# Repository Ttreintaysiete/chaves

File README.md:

# chaves
Cheap Hacky Audio/Video - Glitch VGA synth based on jonasbers.com/chav/

This is a WIP, and PCBs have not fully tested, if you want to contribute send a build to your favorite pcb provider and give us any feedback.

Pending...

* will generate a bom
* building guide

## Chaves

Its a glitch video synth bassed on CHA/V as stated, but with lots of controls and patcheable pins with the intentions of doing a mini-modular video glitch synth.

Like in the original CHA/V it has 6 VCOs, with selectables ranges, sync sources, frequency and effects outputs (thanks to the coupling caps). Here is a schematic of a single voice

* The __syncbus__ can be either connected to the vsyn or hsync of the VGA tester. This will send the selected sync to the jumperpins near the beggining of the Oscillator so you can either select each oscillator to be connected to this sync bus or not to be free running.
* Since we are using pinheaders you can use patcables from any point of the pcb so anthoer oscillator can __modulate__ the sync of a specific oscillator...
* Every voice output can be connected to any of the RGA VGA inputs with patchables, or can be patched somewhere else, to create complex patterns

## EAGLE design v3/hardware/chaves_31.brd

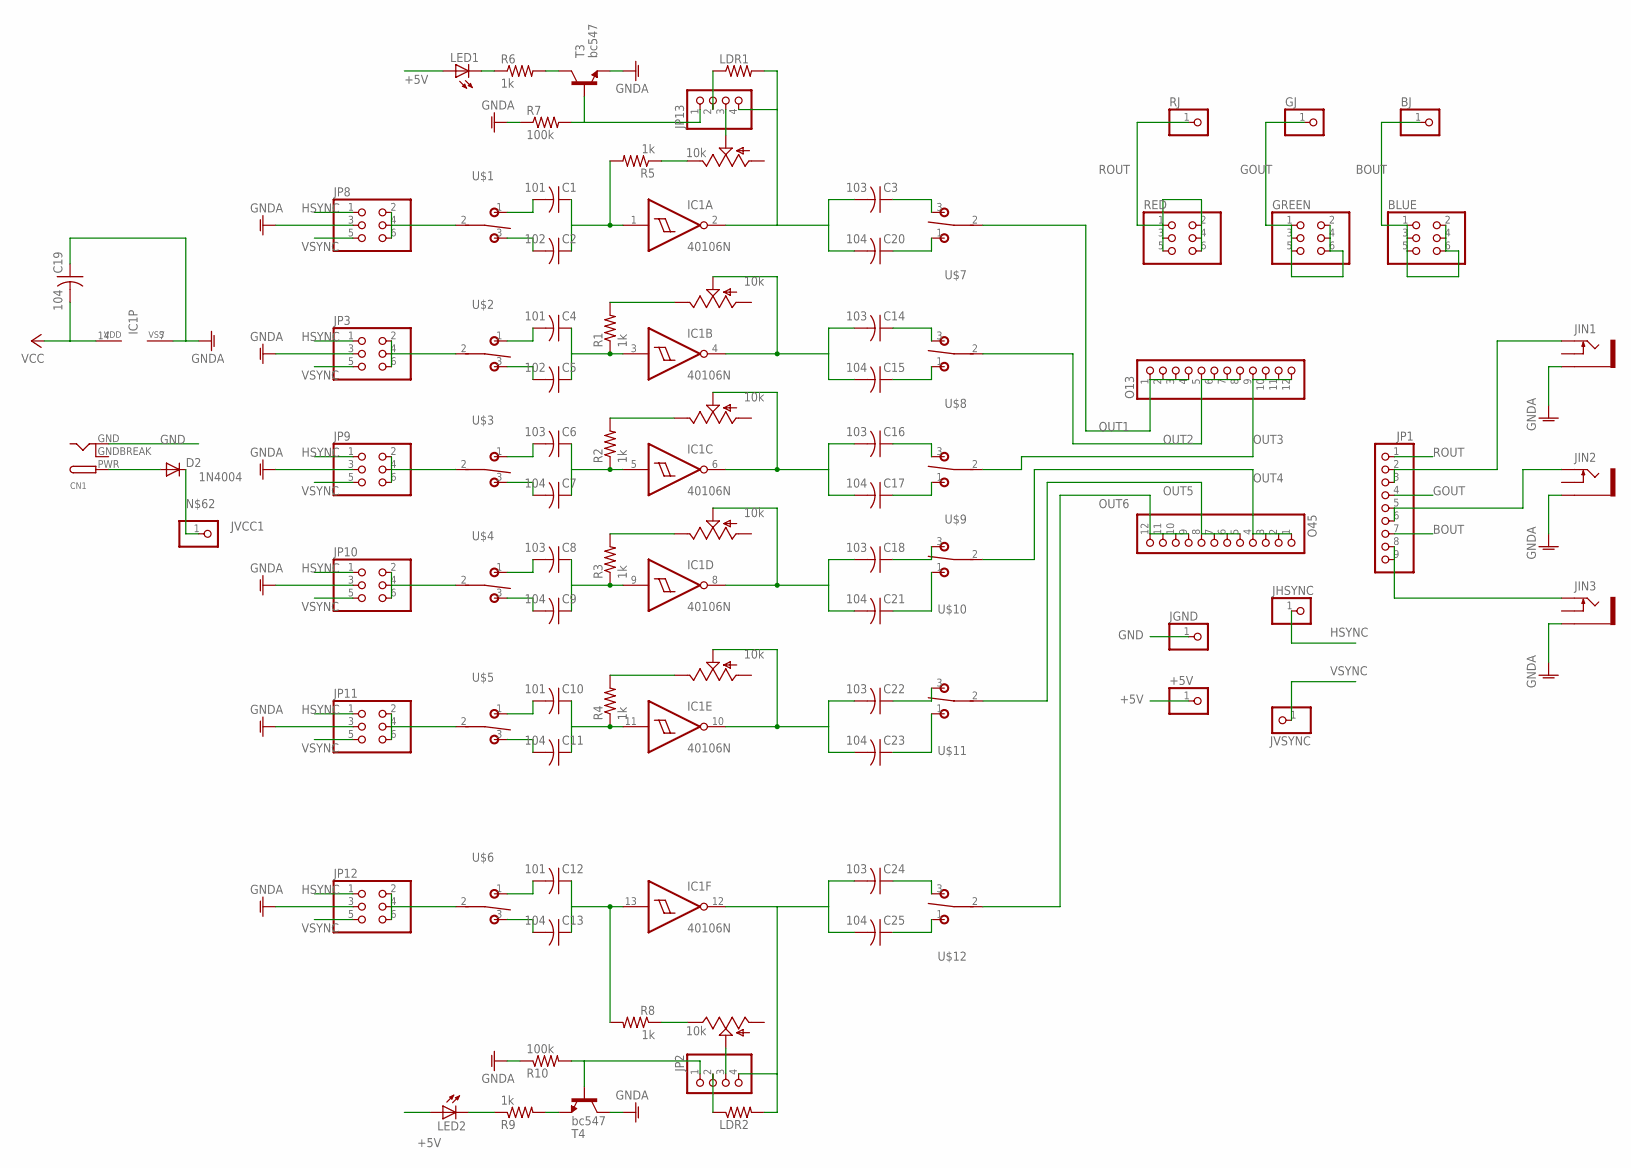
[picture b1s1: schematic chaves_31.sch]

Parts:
+5V: PINHD-1X1; 1X01
BJ: PINHD-1X1; 1X01
BLUE: PINHD-2X3; 2X03
C1, C4, C10, C12: 101; C050-025X075
C2, C5: 102; C050-025X075
C3, C6, C8, C14, C16, C18, C22, C24: 103; C050-025X075
C7, C9, C11, C13, C15, C17, C19, C20, C21, C23, C25: 104; C050-025X075
CN1: DCBARRELPTH; DCJACK_2MM_PTH
D2: 1N4004; DO41-10
GJ: PINHD-1X1; 1X01
GREEN: PINHD-2X3; 2X03
IC1: 40106N; DIL14
JGND: PINHD-1X1; 1X01
JHSYNC: PINHD-1X1; 1X01
JIN1, JIN2, JIN3: PJ302M
JP1: PINHD-1X9; 1X09-BIG
JP2, JP13: PINHD-1X4; 1X04
JP3, JP8, JP9, JP10, JP11, JP12: PINHD-2X3; 2X03
JVCC1: PINHD-1X1; 1X01
JVSYNC: PINHD-1X1; 1X01
LDR1, LDR2: R-US_0204/2V; 0204V
LED1, LED2: LED5MM
O13, O45: PINHD-1X12-CB; 1X12-CB
POT1, POT2, POT3, POT4, POT5, POT6: 10k; ALPS_POT_VERTICAL
R1, R2, R3, R4, R5, R6, R8, R9: 1k; 0204V
R7, R10: 100k; 0204V
RED: PINHD-2X3; 2X03
RJ: PINHD-1X1; 1X01
T3, T4: bc547; TO92-CBE
U$1, U$2, U$3, U$4, U$5, U$6, U$7, U$8, U$9, U$10, U$11, U$12: T-80-T-SPDT-ON-OFF-ON; M9040P

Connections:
+5V: +5V.1, C19.2, IC1.14 (VDD), LED1.A, LED2.A
BOUT: BJ.1, BLUE.1, BLUE.2, BLUE.3, BLUE.4, BLUE.5, BLUE.6, JP1.7
GND: C19.1, CN1.GND, IC1.7 (VSS), JGND.1, JIN1.GND (SLEEVE), JIN2.GND (SLEEVE), JIN3.GND (SLEEVE), JP3.3, JP8.3, JP9.3, JP10.3, JP11.3, JP12.3, R7.1, R10.1, T3.E, T4.C
GNDBREAK: CN1.GNDBREAK
GOUT: GJ.1, GREEN.1, GREEN.2, GREEN.3, GREEN.4, GREEN.5, GREEN.6, JP1.4
HSYNC: JHSYNC.1, JP3.1, JP8.1, JP9.1, JP10.1, JP11.1, JP12.1
unnamed: C1.2, U$1.1 (O)
unnamed: C2.2, U$1.3 (S)
unnamed: JP13.2, LDR1.1
unnamed: C5.2, U$2.3 (S)
unnamed: C4.2, U$2.1 (O)
unnamed: JP13.3, POT1.P$2 (S)
unnamed: C8.2, U$4.1 (O)
unnamed: C9.2, U$4.3 (S)
unnamed: JIN1.TIP, JP1.2, JP1.3
unnamed: C6.2, U$3.1 (O)
unnamed: C7.2, U$3.3 (S)
unnamed: JIN2.TIP, JP1.5, JP1.6
unnamed: JIN3.TIP, JP1.8, JP1.9
unnamed: JP3.2, JP3.4, JP3.6, U$2.2
unnamed: R6.2, T3.C
unnamed: C20.1, U$7.1 (O)
unnamed: C3.1, U$7.3 (S)
unnamed: LED1.K (C), R6.1
unnamed: POT1.P$1 (E), R5.1
unnamed: JP8.2, JP8.4, JP8.6, U$1.2
unnamed: LED2.K (C), R9.1
unnamed: POT2.P$1 (E), R1.2
unnamed: JP9.2, JP9.4, JP9.6, U$3.2
unnamed: C15.1, U$8.1 (O)
unnamed: R9.2, T4.E
unnamed: C14.1, U$8.3 (S)
unnamed: C17.1, U$9.1 (O)
unnamed: C16.1, U$9.3 (S)
unnamed: JP10.2, JP10.4, JP10.6, U$4.2
unnamed: JP13.1, R7.2, T3.B
unnamed: POT3.P$1 (E), R2.2
unnamed: JP11.2, JP11.4, JP11.6, U$5.2
unnamed: JP12.2, JP12.4, JP12.6, U$6.2
unnamed: C21.1, U$10.1 (O)
unnamed: C18.1, U$10.3 (S)
unnamed: C23.1, U$11.1 (O)
unnamed: C22.1, U$11.3 (S)
unnamed: C25.1, U$12.1 (O)
unnamed: C24.1, U$12.3 (S)
unnamed: C10.2, U$5.1 (O)
unnamed: POT4.P$1 (E), R3.2
unnamed: C11.2, U$5.3 (S)
unnamed: C13.2, U$6.3 (S)
unnamed: C12.2, U$6.1 (O)
unnamed: POT5.P$1 (E), R4.2
unnamed: C24.2, C25.2, IC1.12 (O), JP2.4, LDR2.2
unnamed: JP2.2, LDR2.1
unnamed: JP2.3, POT6.P$2 (S)
unnamed: POT6.P$1 (E), R8.1
unnamed: JP2.1, R10.2, T4.B
unnamed: D2.C, JVCC1.1
unnamed: C3.2, C20.2, IC1.2 (O), JP13.4, LDR1.2
unnamed: C14.2, C15.2, IC1.4 (O), POT2.P$2 (S)
unnamed: C16.2, C17.2, IC1.6 (O), POT3.P$2 (S)
unnamed: C18.2, C21.2, IC1.8 (O), POT4.P$2 (S)
unnamed: C22.2, C23.2, IC1.10 (O), POT5.P$2 (S)
OUT1: O13.1, O13.2, O13.3, O13.4, U$7.2
OUT2: O13.5, O13.6, O13.7, O13.8, U$8.2
OUT3: O13.9, O13.10, O13.11, O13.12, U$9.2
OUT4: O45.1, O45.2, O45.3, O45.4, U$10.2
OUT5: O45.5, O45.6, O45.7, O45.8, U$11.2
OUT6: O45.9, O45.10, O45.11, O45.12, U$12.2
ROUT: JP1.1, RED.1, RED.2, RED.3, RED.4, RED.5, RED.6, RJ.1
SS1: C1.1, C2.1, IC1.1 (I), R5.2
SS2: C4.1, C5.1, IC1.3 (I), R1.1
SS3: C6.1, C7.1, IC1.5 (I), R2.1
SS4: C8.1, C9.1, IC1.9 (I), R3.1
SS5: C10.1, C11.1, IC1.11 (I), R4.1
SS6: C12.1, C13.1, IC1.13 (I), R8.2
VIN: CN1.PWR, D2.A
VSYNC: JP3.5, JP8.5, JP9.5, JP10.5, JP11.5, JP12.5, JVSYNC.1

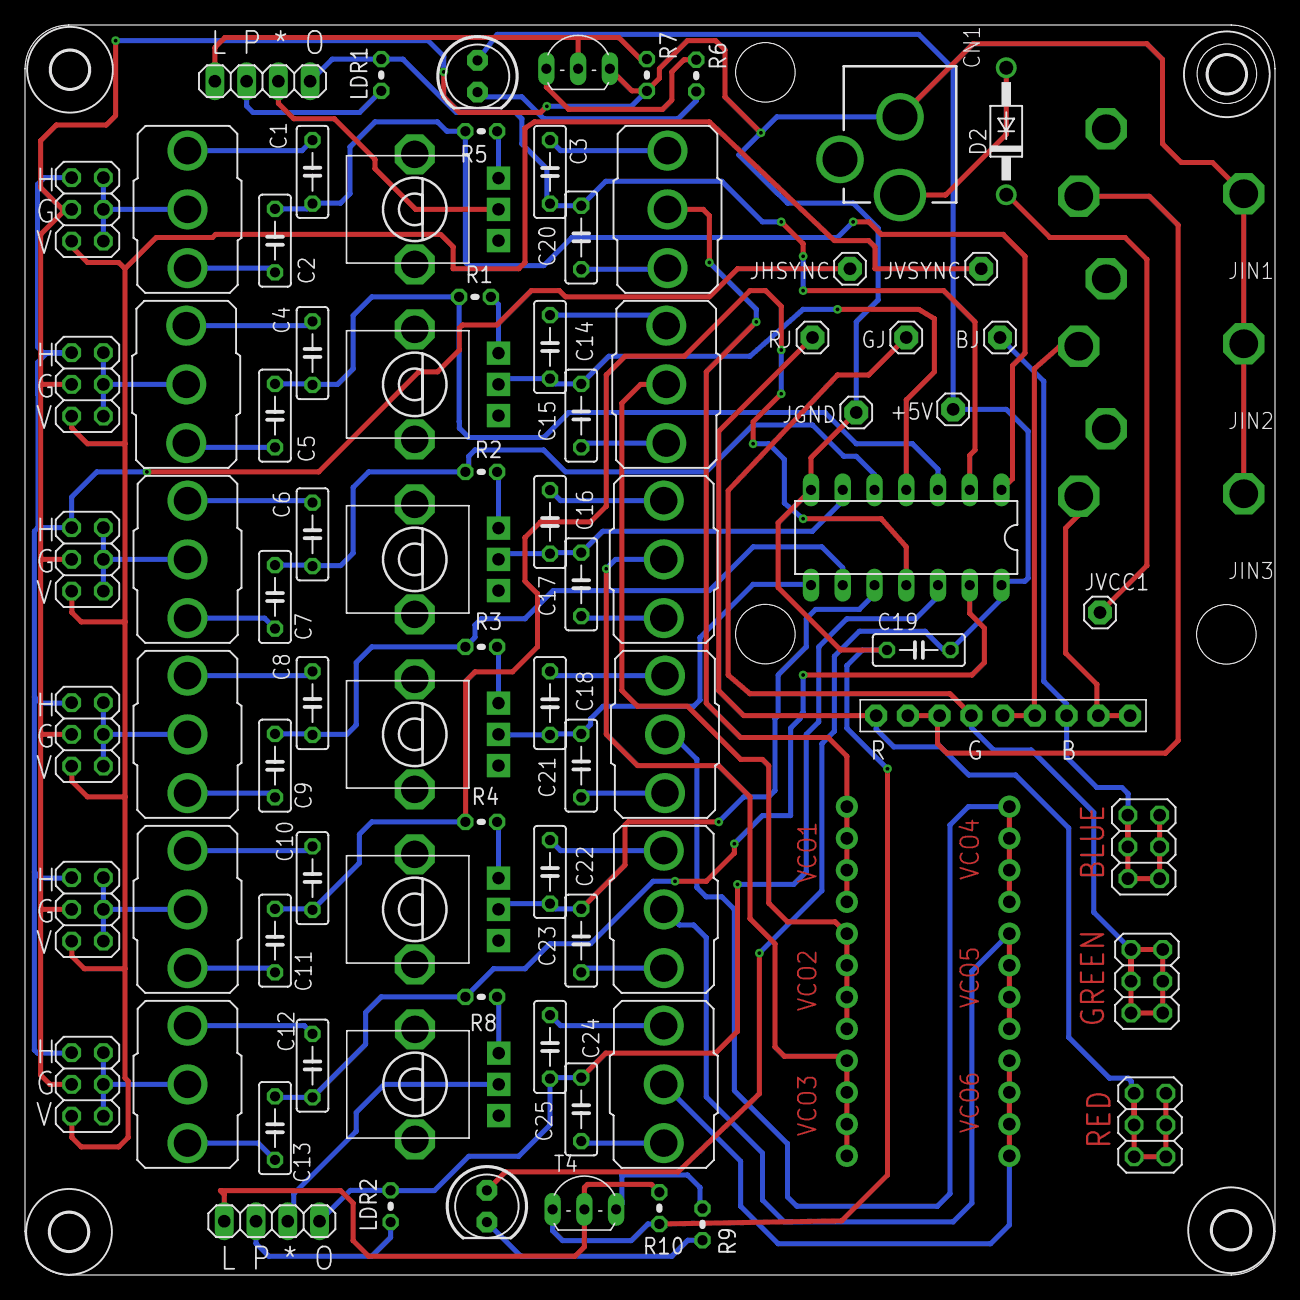
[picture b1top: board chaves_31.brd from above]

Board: 2 copper layers, 100.0 x 100.0 mm, 95 parts (0 on the bottom side), 76 nets.

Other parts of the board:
E$1, E$2, E$3, E$4: DRILL_0.1875
E$5, E$6, E$7, E$8: 3,0

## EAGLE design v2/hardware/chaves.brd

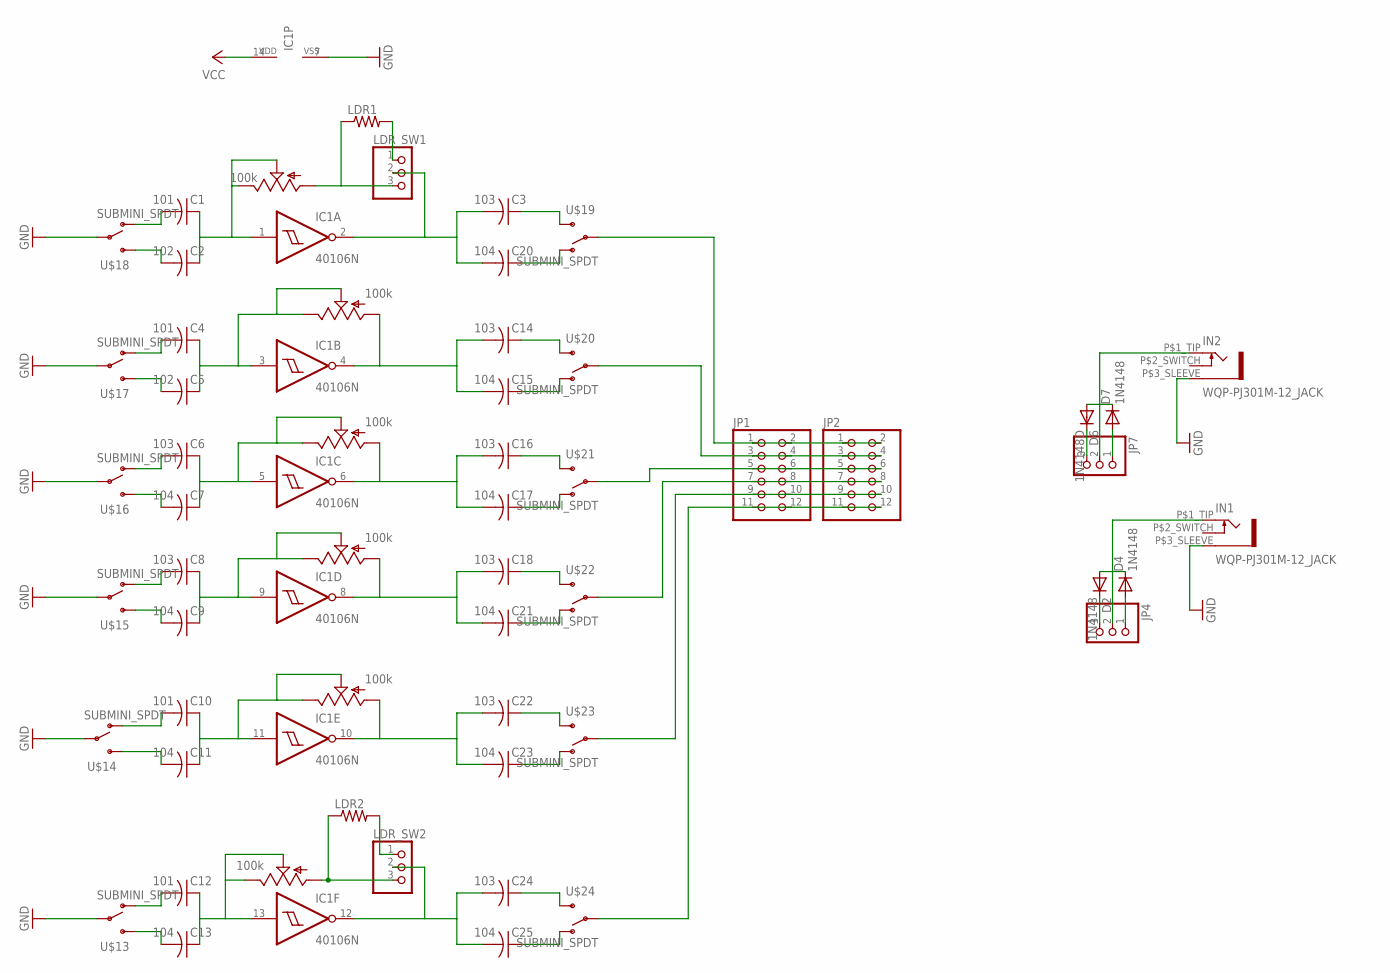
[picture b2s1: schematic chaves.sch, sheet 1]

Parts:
C1, C4, C10, C12: 101; C050-025X075
C2, C5: 102; C050-025X075
C3, C6, C8, C14, C16, C18, C22, C24: 103; C050-025X075
C7, C9, C11, C13, C15, C17, C20, C21, C23, C25: 104; C050-025X075
D2, D4, D7: 1N4148; DO35-7
D6: 1N4148D; DO35-7
IC1: 40106N; DIL14
IN1, IN2: WQP-PJ301M-12_JACK
JP1, JP2: PINHD-2X6; 2X06
JP4, JP7: PINHD-1X3CB; 1X03-CLEANBIG
LDR1, LDR2: R-US_0204/7; 0204/7
LDR_SW1, LDR_SW2: PINHD-1X3; 1X03
POT1, POT2, POT3, POT4, POT5, POT6: 100k; ALPS_POT_VERTICAL
U$13, U$14, U$15, U$16, U$17, U$18, U$19, U$20, U$21, U$22, U$23, U$24: SUBMINI_SPDT; SUBMINI_TOGGLE

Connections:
GND: IC1.7 (VSS), IN1.P$3_SLEEVE (1), IN2.P$3_SLEEVE (1), U$13.COM (COMMON), U$14.COM (COMMON), U$15.COM (COMMON), U$16.COM (COMMON), U$17.COM (COMMON), U$18.COM (COMMON); also elsewhere on the board
GND1: C3.2, C20.2, IC1.2 (O), LDR_SW1.2
GND2: C14.2, C15.2, IC1.4 (O), POT2.P$3 (A)
GND3: C16.2, C17.2, IC1.6 (O), POT3.P$3 (A)
GND4: C18.2, C21.2, IC1.8 (O), POT4.P$3 (A)
GND5: C22.2, C23.2, IC1.10 (O), POT5.P$3 (A)
GND6: C24.2, C25.2, IC1.12 (O), LDR_SW2.2
unnamed: C1.2, U$18.1 (O)
unnamed: C2.2, U$18.3 (S)
unnamed: LDR2.2, LDR_SW2.1
unnamed: C5.2, U$17.3 (S)
unnamed: C4.2, U$17.1 (O)
unnamed: LDR1.2, LDR_SW1.1
unnamed: C8.2, U$15.1 (O)
unnamed: C9.2, U$15.3 (S)
unnamed: D6.A, D7.C, IN2.P$1_TIP (2), JP7.2
unnamed: C6.2, U$16.1 (O)
unnamed: C7.2, U$16.3 (S)
unnamed: C20.1, U$19.1 (O)
unnamed: C3.1, U$19.3 (S)
unnamed: JP1.1, JP1.2, JP2.1, JP2.2, U$19.COM (COMMON)
unnamed: LDR1.1, LDR_SW1.3, POT1.P$3 (A)
unnamed: LDR2.1, LDR_SW2.3, POT6.P$3 (A)
unnamed: D2.A, D4.C, IN1.P$1_TIP (2), JP4.2
unnamed: C15.1, U$20.1 (O)
unnamed: C14.1, U$20.3 (S)
unnamed: JP1.3, JP1.4, JP2.3, JP2.4, U$20.COM (COMMON)
unnamed: C17.1, U$21.1 (O)
unnamed: C16.1, U$21.3 (S)
unnamed: JP1.5, JP1.6, JP2.5, JP2.6, U$21.COM (COMMON)
unnamed: C1.1, C2.1, IC1.1 (I), POT1.P$1 (E), POT1.P$2 (S)
unnamed: C4.1, C5.1, IC1.3 (I), POT2.P$1 (E), POT2.P$2 (S)
unnamed: C6.1, C7.1, IC1.5 (I), POT3.P$1 (E), POT3.P$2 (S)
unnamed: C8.1, C9.1, IC1.9 (I), POT4.P$1 (E), POT4.P$2 (S)
unnamed: C21.1, U$22.1 (O)
unnamed: C18.1, U$22.3 (S)
unnamed: JP1.7, JP1.8, JP2.7, JP2.8, U$22.COM (COMMON)
unnamed: C23.1, U$23.1 (O)
unnamed: C22.1, U$23.3 (S)
unnamed: JP1.9, JP1.10, JP2.9, JP2.10, U$23.COM (COMMON)
unnamed: C25.1, U$24.1 (O)
unnamed: C24.1, U$24.3 (S)
unnamed: JP1.11, JP1.12, JP2.11, JP2.12, U$24.COM (COMMON)
unnamed: C10.2, U$14.1 (O)
unnamed: C10.1, C11.1, IC1.11 (I), POT5.P$1 (E), POT5.P$2 (S)
unnamed: C11.2, U$14.3 (S)
unnamed: C13.2, U$13.3 (S)
unnamed: C12.2, U$13.1 (O)
unnamed: C12.1, C13.1, IC1.13 (I), POT6.P$1 (E), POT6.P$2 (S)
unnamed: D2.C, JP4.3
unnamed: D4.A, JP4.1
unnamed: D6.C, JP7.3
unnamed: D7.A, JP7.1
VCC: IC1.14 (VDD); also elsewhere on the board

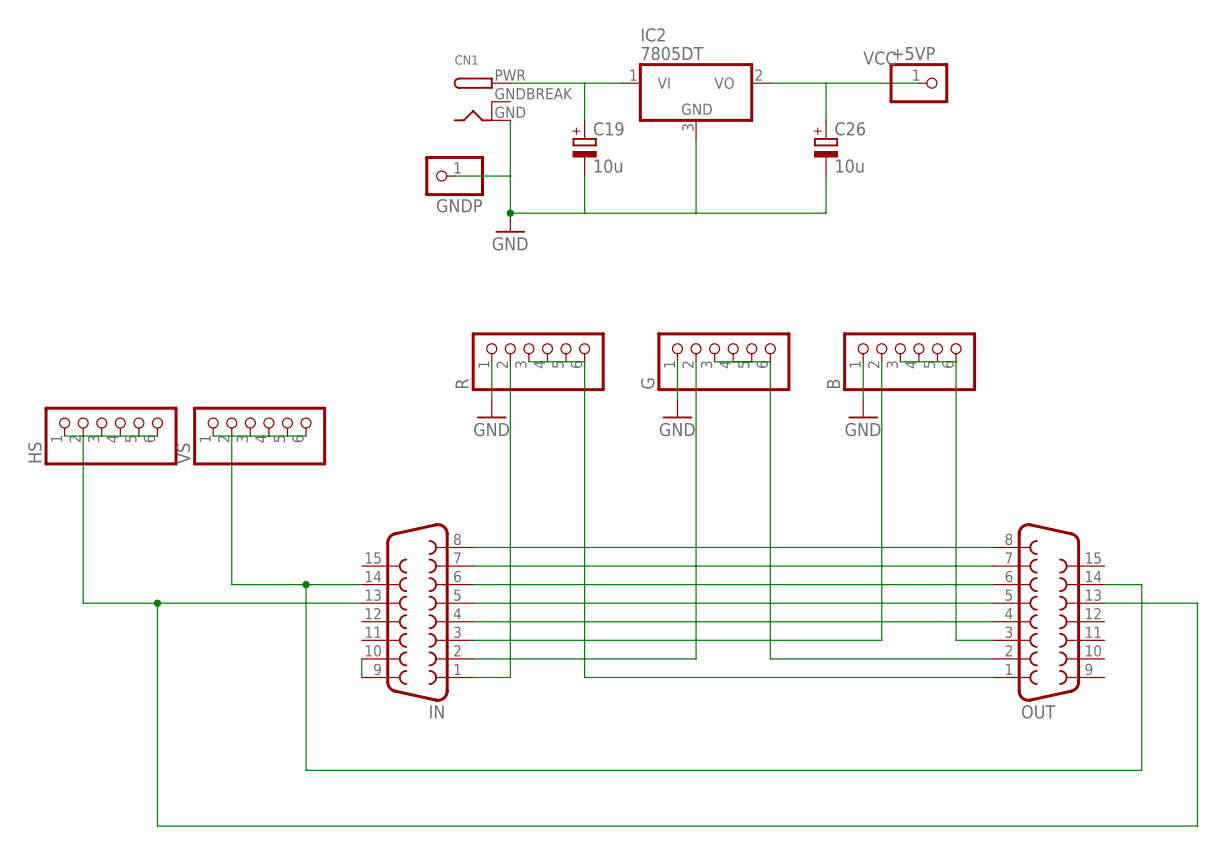
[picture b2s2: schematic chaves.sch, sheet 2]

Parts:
+5VP: PINHD-1X1CB; 1X01-CLEANBIG
B: PINHD-1X6CLEAN; 1X06-CLEAN
C19, C26: 10u; E2,5-5
CN1: DCBARRELPTH; DCJACK_2MM_PTH
G: PINHD-1X6CLEAN; 1X06-CLEAN
GNDP: PINHD-1X1CB; 1X01-CLEANBIG
HS: PINHD-1X6CLEAN; 1X06-CLEAN
IC2: 7805DT; TO252
IN: F15HDH; HDF15H
OUT: F15HDH; HDF15H
R: PINHD-1X6CLEAN; 1X06-CLEAN
VS: PINHD-1X6CLEAN; 1X06-CLEAN

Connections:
GND: B.1, C19.-, C26.-, CN1.GND, G.1, GNDP.1, IC2.3 (GND), IN.4, IN.5, IN.6, IN.7, IN.8, IN.9, IN.10, OUT.4, OUT.5, OUT.6, OUT.7, OUT.8, R.1; also elsewhere on the board
GNDBREAK: CN1.GNDBREAK
unnamed: IN.1, R.2
unnamed: OUT.1, R.3, R.4, R.5, R.6
unnamed: G.2, IN.2
unnamed: G.3, G.4, G.5, G.6, OUT.2
unnamed: B.2, IN.3
unnamed: B.3, B.4, B.5, B.6, OUT.3
unnamed: IN.14, OUT.14, VS.1, VS.2, VS.3, VS.4, VS.5, VS.6
unnamed: HS.1, HS.2, HS.3, HS.4, HS.5, HS.6, IN.13, OUT.13
unnamed: C19.+, CN1.PWR, IC2.1 (VI)
VCC: +5VP.1, C26.+, IC2.2 (VO); also elsewhere on the board

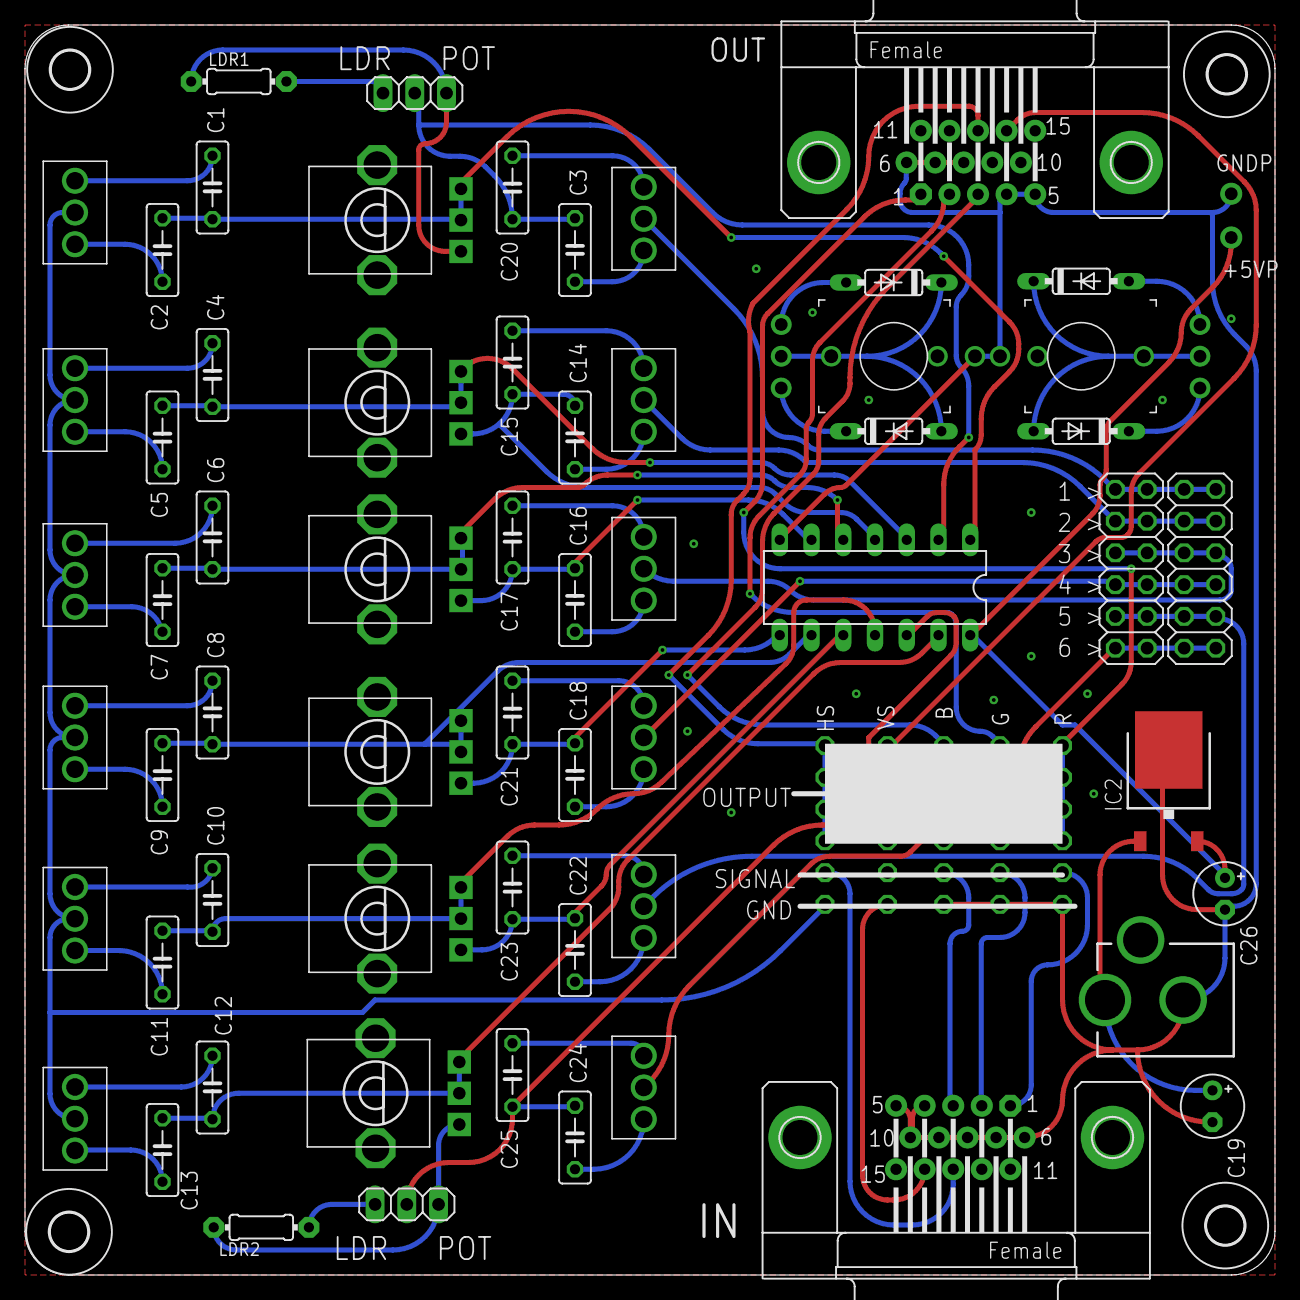
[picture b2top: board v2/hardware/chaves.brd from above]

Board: 2 copper layers, 100.0 x 100.0 mm, 74 parts (0 on the bottom side), 63 nets.

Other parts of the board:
E$1, E$5, E$7, E$8: 3,0

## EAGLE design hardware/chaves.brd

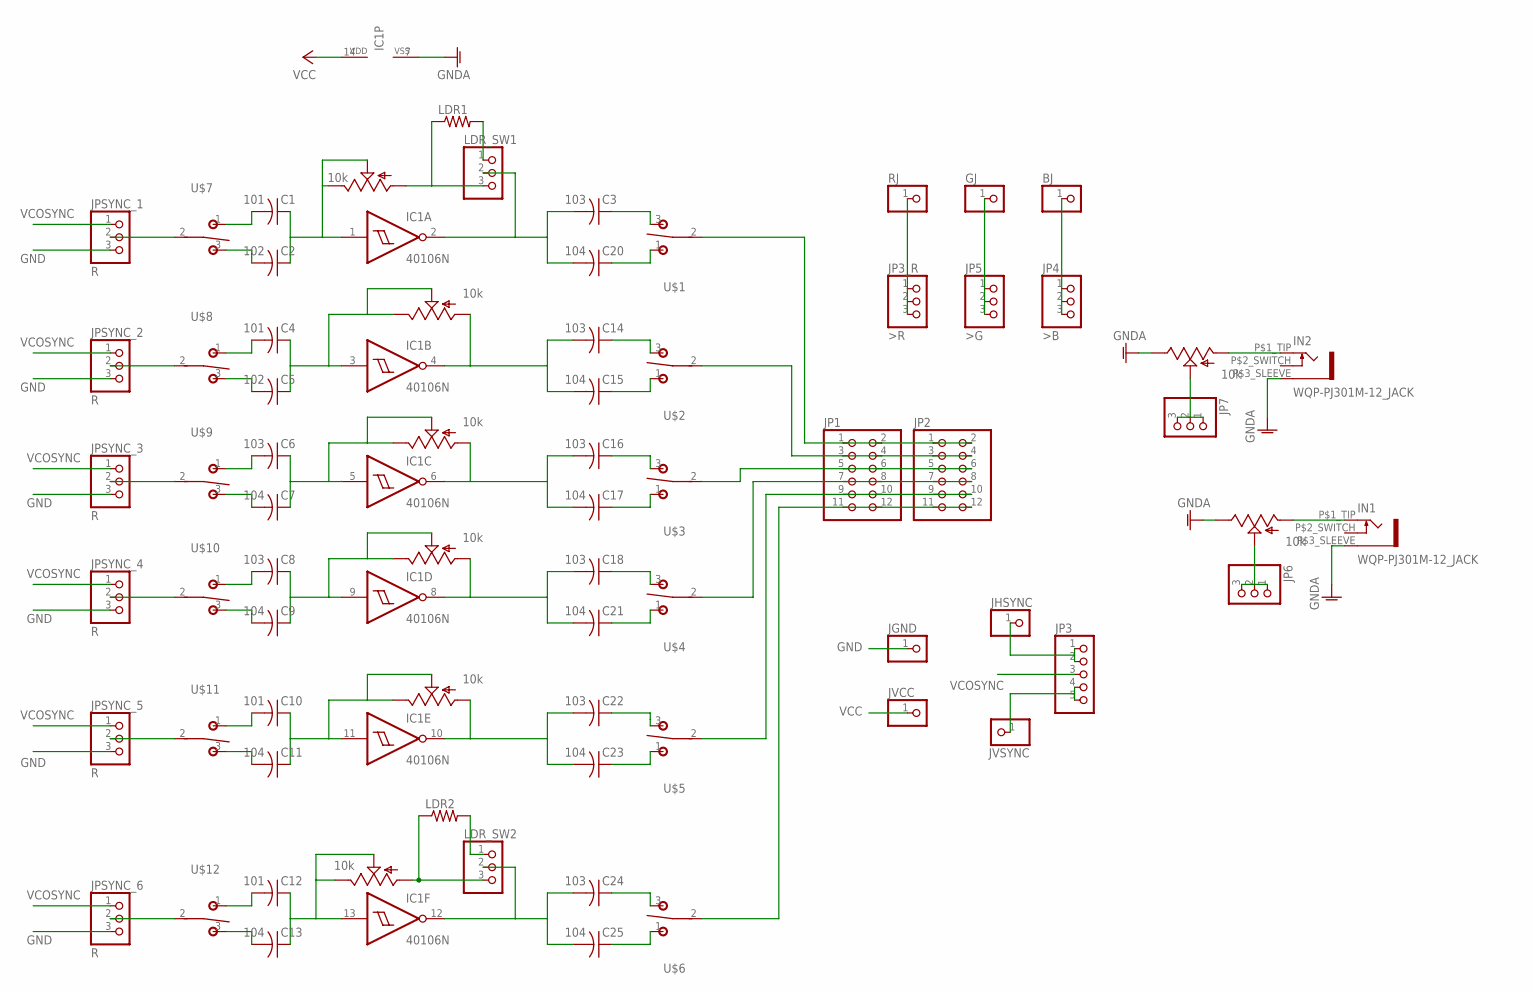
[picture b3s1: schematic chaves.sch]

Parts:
BJ: PINHD-1X1; 1X01
C1, C4, C10, C12: 101; C050-025X075
C2, C5: 102; C050-025X075
C3, C6, C8, C14, C16, C18, C22, C24: 103; C050-025X075
C7, C9, C11, C13, C15, C17, C20, C21, C23, C25: 104; C050-025X075
GJ: PINHD-1X1; 1X01
IC1: 40106N; DIL14
IN1, IN2: WQP-PJ301M-12_JACK
JGND: PINHD-1X1; 1X01
JHSYNC: PINHD-1X1; 1X01
JP1, JP2: PINHD-2X6; 2X06
JP3: PINHD-1X5; 1X05
JP3_R: >R; 1X03
JP4: >B; 1X03
JP5: >G; 1X03
JP6, JP7: PINHD-1X3CB; 1X03-CLEANBIG
JPSYNC_1, JPSYNC_2, JPSYNC_3, JPSYNC_4, JPSYNC_5, JPSYNC_6: R; 1X03
JVCC: PINHD-1X1; 1X01
JVSYNC: PINHD-1X1; 1X01
LDR1, LDR2: R-US_0204/7; 0204/7
LDR_SW1, LDR_SW2: PINHD-1X3; 1X03
POT1, POT2, POT3, POT4, POT5, POT6, POT7, POT8: 10k; ALPS_POT_VERTICAL
RJ: PINHD-1X1; 1X01
U$1, U$2, U$3, U$4, U$5, U$6, U$7, U$8, U$9, U$10, U$11, U$12: T-80-T-SPDT-ON-OFF-ON; M9040P

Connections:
GND: IC1.7 (VSS), IN1.P$3_SLEEVE (1), IN2.P$3_SLEEVE (1), JGND.1, JPSYNC_1.3, JPSYNC_2.3, JPSYNC_3.3, JPSYNC_4.3, JPSYNC_5.3, JPSYNC_6.3, POT7.P$1 (E), POT8.P$1 (E)
GND1: C3.2, C20.2, IC1.2 (O), LDR_SW1.2
GND2: C14.2, C15.2, IC1.4 (O), POT2.P$3 (A)
GND3: C16.2, C17.2, IC1.6 (O), POT3.P$3 (A)
GND4: C18.2, C21.2, IC1.8 (O), POT4.P$3 (A)
GND5: C22.2, C23.2, IC1.10 (O), POT5.P$3 (A)
GND6: C24.2, C25.2, IC1.12 (O), LDR_SW2.2
unnamed: C1.2, U$7.1 (O)
unnamed: C2.2, U$7.3 (S)
unnamed: LDR2.2, LDR_SW2.1
unnamed: C5.2, U$8.3 (S)
unnamed: C4.2, U$8.1 (O)
unnamed: LDR1.2, LDR_SW1.1
unnamed: C8.2, U$10.1 (O)
unnamed: C9.2, U$10.3 (S)
unnamed: IN2.P$1_TIP (2), POT8.P$3 (A)
unnamed: C6.2, U$9.1 (O)
unnamed: C7.2, U$9.3 (S)
unnamed: JP6.1, JP6.2, JP6.3, POT7.P$2 (S)
unnamed: BJ.1, JP4.1, JP4.2, JP4.3
unnamed: GJ.1, JP5.1, JP5.2, JP5.3
unnamed: JP3_R.1, JP3_R.2, JP3_R.3, RJ.1
unnamed: C20.1, U$1.1 (O)
unnamed: C3.1, U$1.3 (S)
unnamed: JP1.1, JP1.2, JP2.1, JP2.2, U$1.2
unnamed: LDR1.1, LDR_SW1.3, POT1.P$3 (A)
unnamed: JHSYNC.1, JP3.1, JP3.2
unnamed: JP3.4, JP3.5, JVSYNC.1
unnamed: LDR2.1, LDR_SW2.3, POT6.P$3 (A)
unnamed: IN1.P$1_TIP (2), POT7.P$3 (A)
unnamed: C15.1, U$2.1 (O)
unnamed: JP7.1, JP7.2, JP7.3, POT8.P$2 (S)
unnamed: C14.1, U$2.3 (S)
unnamed: JP1.3, JP1.4, JP2.3, JP2.4, U$2.2
unnamed: C17.1, U$3.1 (O)
unnamed: C16.1, U$3.3 (S)
unnamed: JP1.5, JP1.6, JP2.5, JP2.6, U$3.2
unnamed: C1.1, C2.1, IC1.1 (I), POT1.P$1 (E), POT1.P$2 (S)
unnamed: C4.1, C5.1, IC1.3 (I), POT2.P$1 (E), POT2.P$2 (S)
unnamed: C6.1, C7.1, IC1.5 (I), POT3.P$1 (E), POT3.P$2 (S)
unnamed: C8.1, C9.1, IC1.9 (I), POT4.P$1 (E), POT4.P$2 (S)
unnamed: C21.1, U$4.1 (O)
unnamed: C18.1, U$4.3 (S)
unnamed: JP1.7, JP1.8, JP2.7, JP2.8, U$4.2
unnamed: C23.1, U$5.1 (O)
unnamed: C22.1, U$5.3 (S)
unnamed: JP1.9, JP1.10, JP2.9, JP2.10, U$5.2
unnamed: C25.1, U$6.1 (O)
unnamed: C24.1, U$6.3 (S)
unnamed: JP1.11, JP1.12, JP2.11, JP2.12, U$6.2
unnamed: C10.2, U$11.1 (O)
unnamed: C10.1, C11.1, IC1.11 (I), POT5.P$1 (E), POT5.P$2 (S)
unnamed: C11.2, U$11.3 (S)
unnamed: C13.2, U$12.3 (S)
unnamed: C12.2, U$12.1 (O)
unnamed: C12.1, C13.1, IC1.13 (I), POT6.P$1 (E), POT6.P$2 (S)
SS1: JPSYNC_1.2, U$7.2
SS2: JPSYNC_2.2, U$8.2
SS3: JPSYNC_3.2, U$9.2
SS4: JPSYNC_4.2, U$10.2
SS5: JPSYNC_5.2, U$11.2
SS6: JPSYNC_6.2, U$12.2
VCC: IC1.14 (VDD), JVCC.1
VCOSYNC: JP3.3, JPSYNC_1.1, JPSYNC_2.1, JPSYNC_3.1, JPSYNC_4.1, JPSYNC_5.1, JPSYNC_6.1

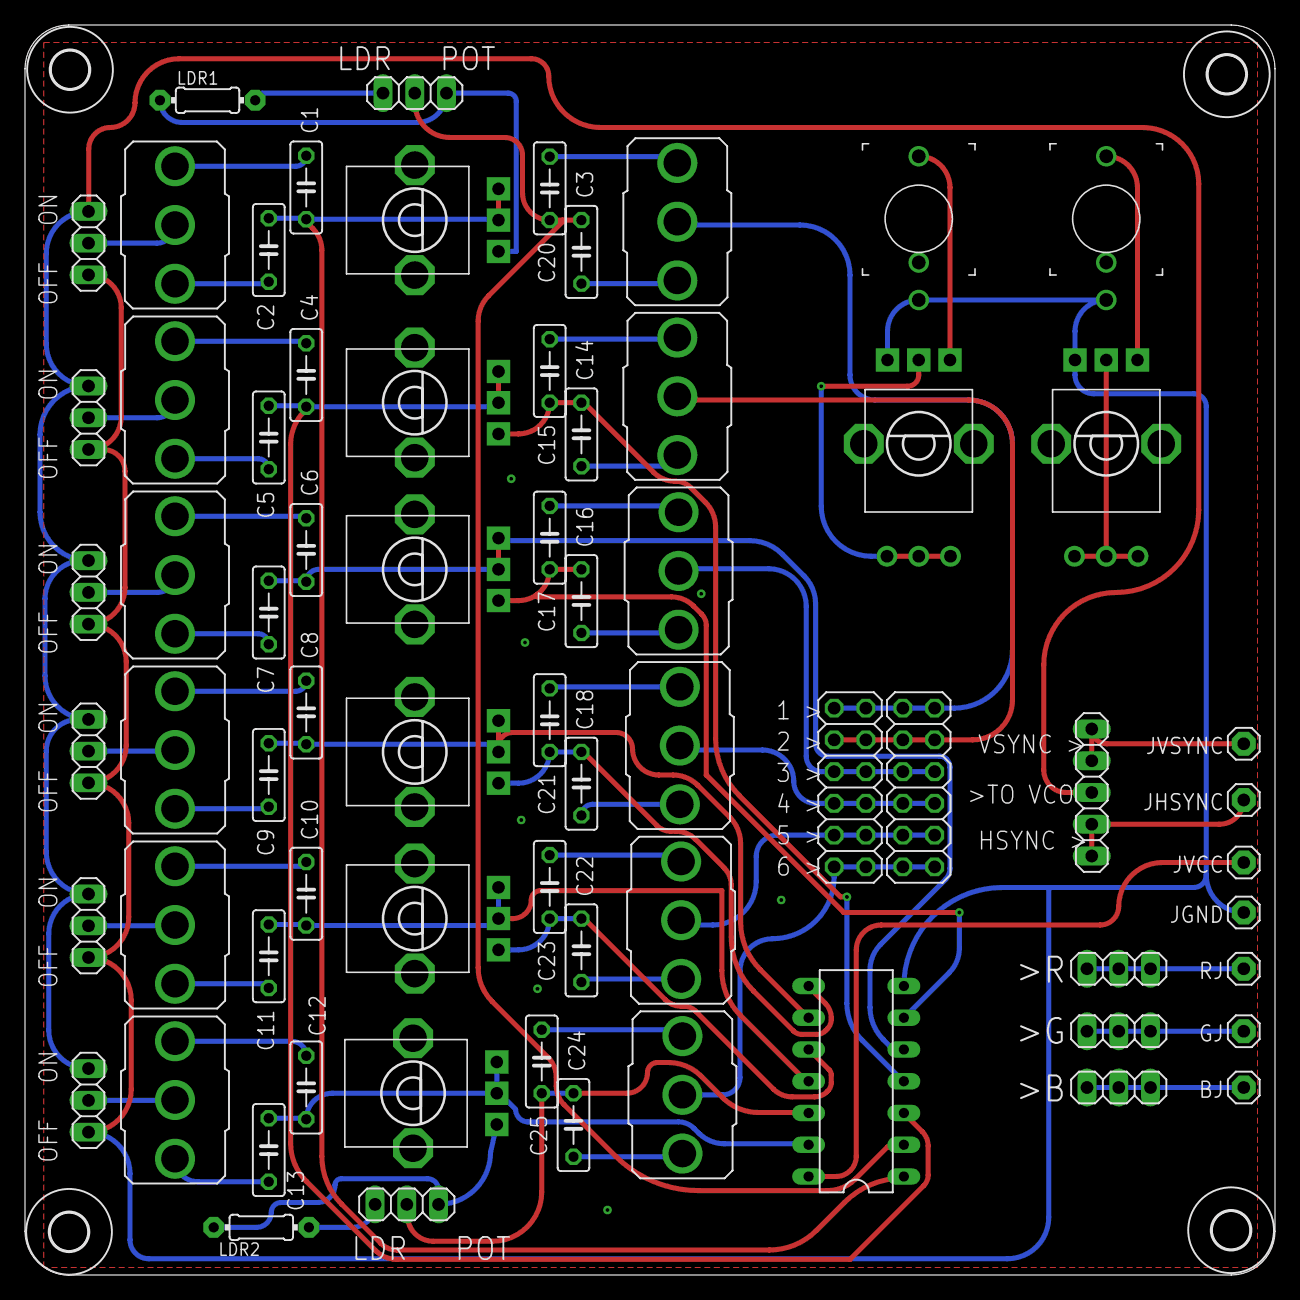
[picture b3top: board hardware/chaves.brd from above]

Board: 2 copper layers, 100.0 x 100.0 mm, 76 parts (0 on the bottom side), 64 nets.

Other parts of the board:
E$5, E$6, E$7, E$8: 3,0

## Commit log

2017-12-13 Initial commit with gerber files
2017-12-13 Adding fixed texts layers
2017-12-22 Updating schematic pdf and adding single voice diagram
2017-12-22 Adding image to README
2017-12-22 Adding some descriptions...
2017-12-22 Addign more useless text
2018-01-06 all done except ground plane
2018-01-06 Ground planed
2018-02-06 new version of chaves
2018-02-06 moving old bom
2018-12-08 Rename and adding v3
2018-12-08 working on position board v3
2018-12-08 minor fixes on text and aligment
2018-12-08 changing pinheaders to connect the trigger in properly
2019-01-02 Finixhed position and merged pins
2019-01-02 fully routed v3, checked errors, layers corrected ready to fav proto
2019-01-04 Revised gerbers for all versions
2019-01-12 Adding updated gerbers
2019-01-16 Adding v3 bom
2019-02-11 renaming for versions
2019-02-11 Adding gerbers for 31 version, fixed many problems of the 3.0: - there was an overlap on the VCO1 feedback line - added a current limiting resistor of 1k - removed the 100k resistors from the voltage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
2019-02-21 Adding labels on bottom
2019-10-31 Add digikey/aliexpress BOM (untested at the moment)
